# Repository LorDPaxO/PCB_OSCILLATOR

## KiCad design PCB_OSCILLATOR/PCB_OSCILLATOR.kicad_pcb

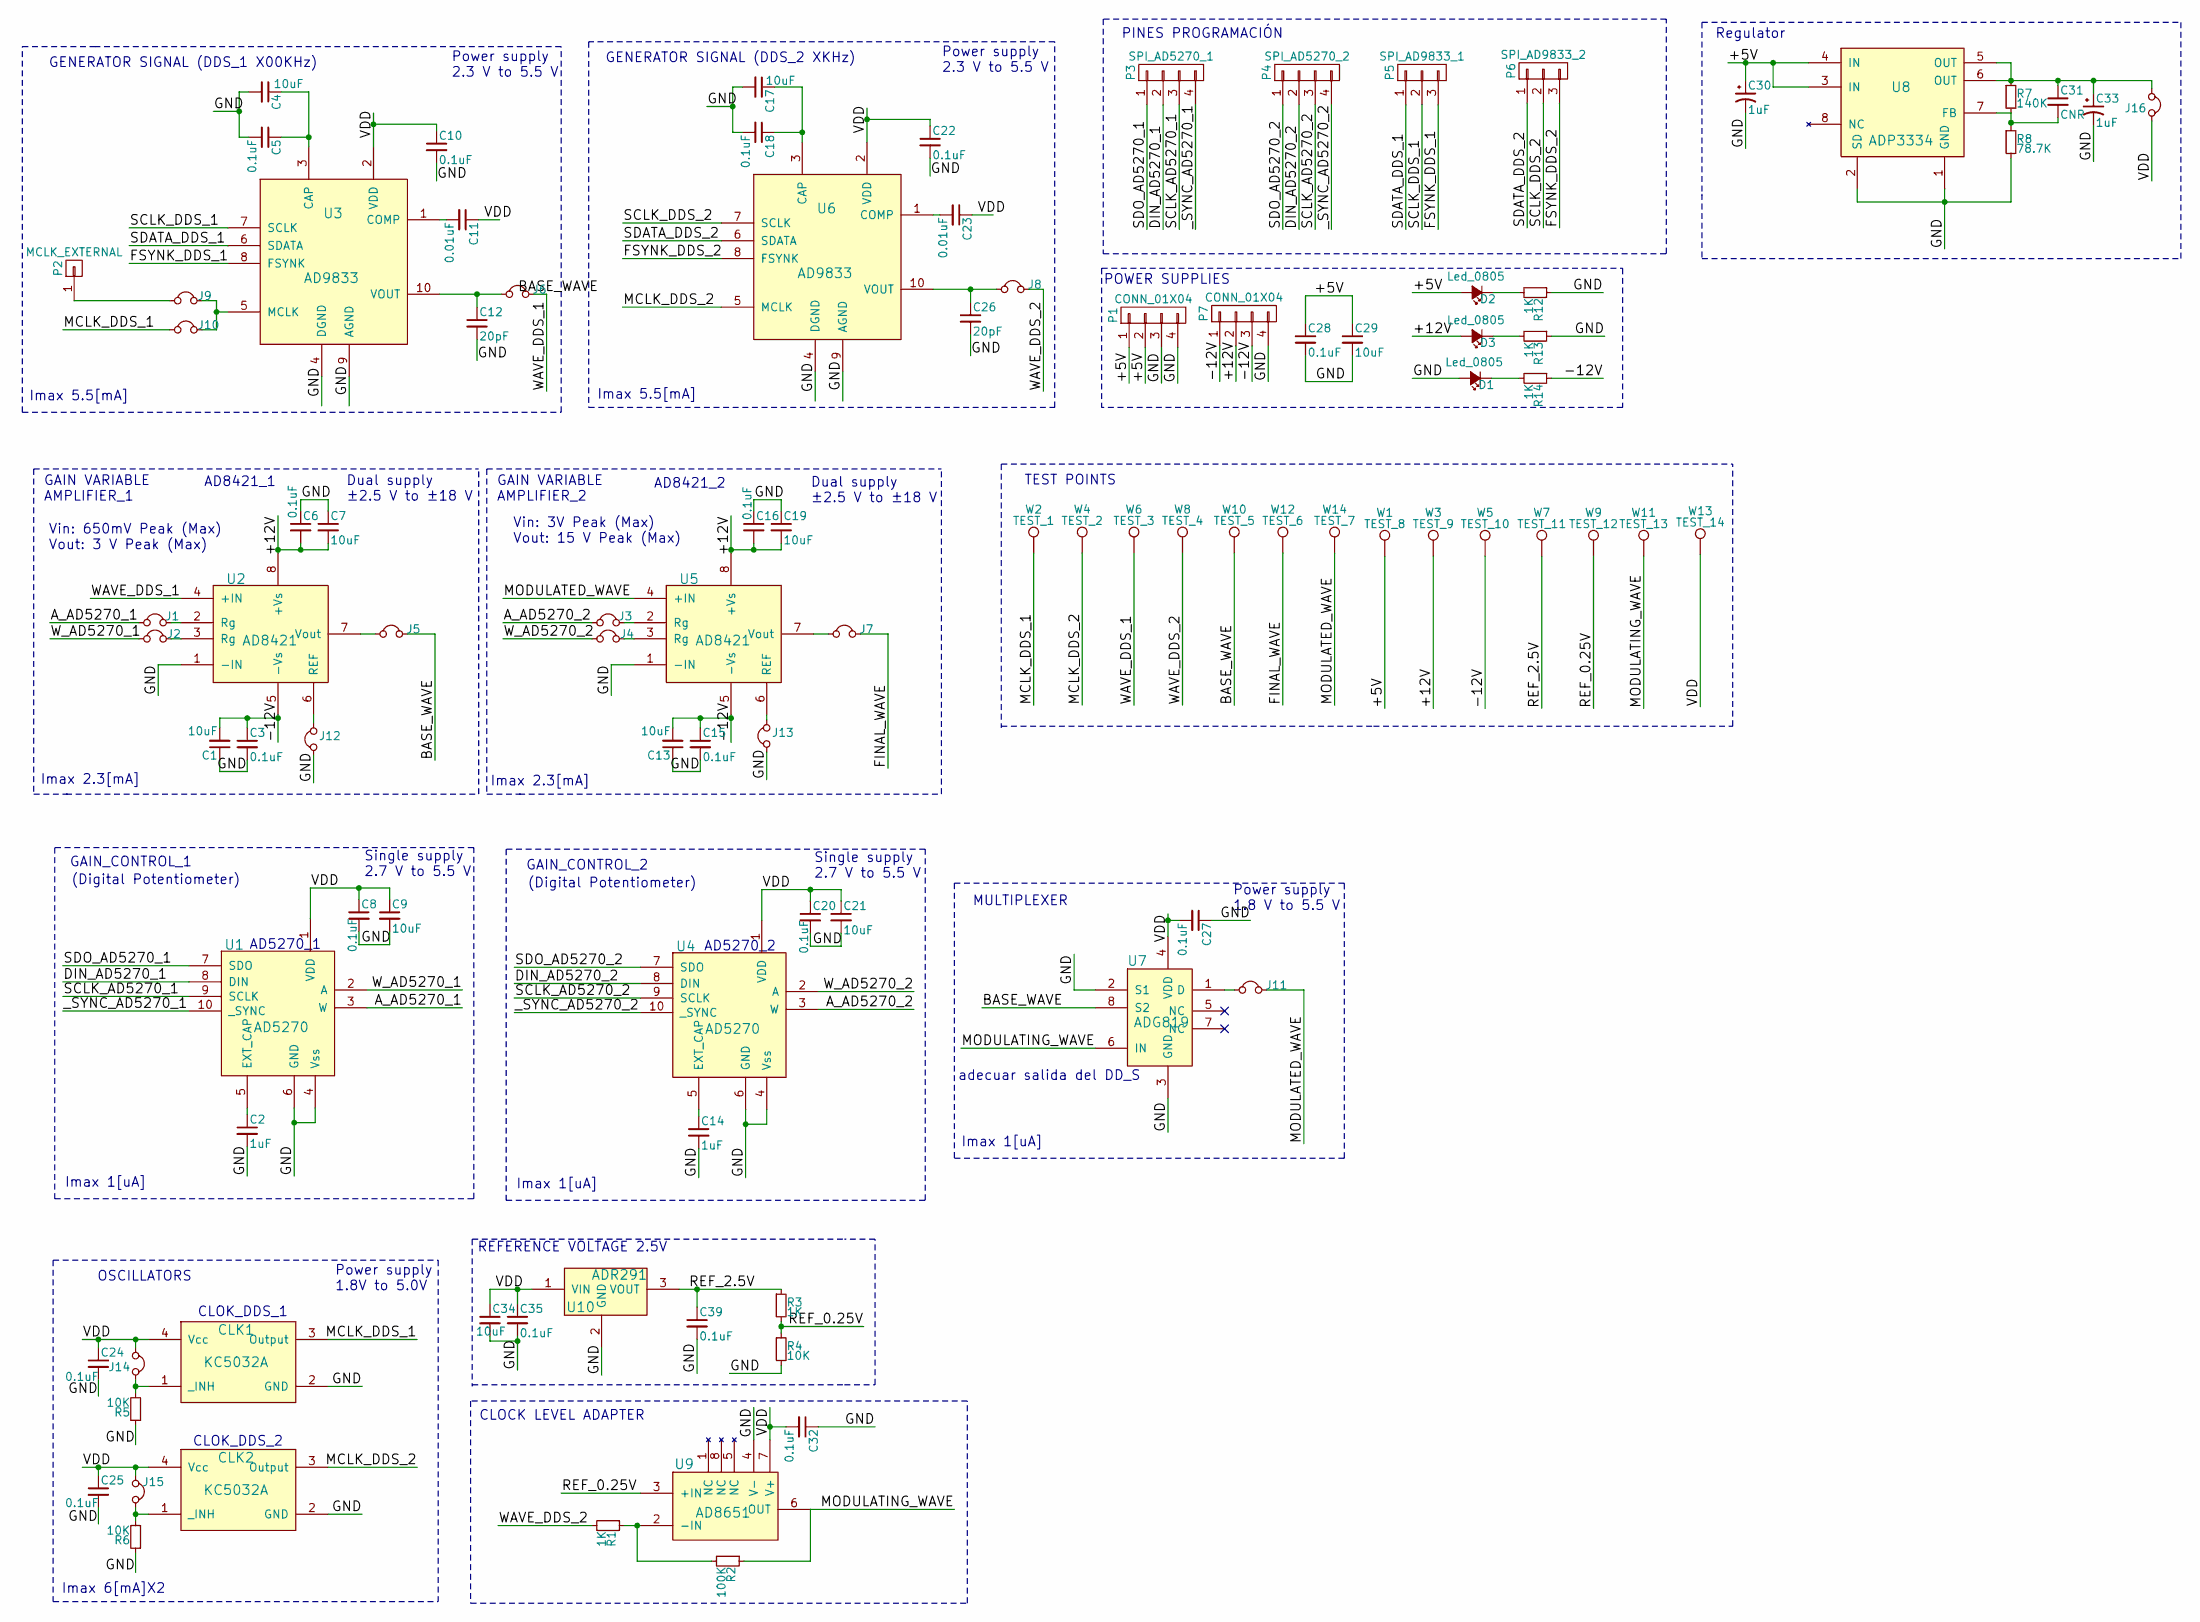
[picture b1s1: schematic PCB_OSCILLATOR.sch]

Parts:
C1, C7, C13, C19, C21: 10uF; C_1206_HandSoldering
C2, C14, C30, C33: 1uF; C_0805_HandSoldering
C3, C5, C6, C8, C10, C15, C16, C18, C20, C22, C24, C25, C27, C28, C32, C35, C39: 0.1uF; C_0805_HandSoldering; Digi-Key Part Number 478-1395-2-ND
C4, C9, C17, C29, C34: 10uF; C_0805_HandSoldering
C11, C23: 0.01uF; C_0805_HandSoldering; Digi-Key Part Number 478-1383-2-ND
C12, C26: 20pF; C_0805_HandSoldering
C31: CNR; C_1206_HandSoldering
CLK1, CLK2: KC5032A; KC5032A_Foot_Print
D1, D2, D3: Led_0805; R_0805_HandSoldering; Digi-Key Part Number 475-1410-2-ND
J1, J2, J3, J4, J5, J6, J7, J8, J9, J10, J11, J12, J13, J14, J15, J16: Jumper; Pin_Header_Straight_1x02
P1, P7: CONN_01X04; Socket_Strip_Straight_1x04
P2: MCLK_EXTERNAL; Socket_Strip_Straight_1x01
P3: SPI_AD5270_1; Socket_Strip_Straight_1x04
P4: SPI_AD5270_2; Socket_Strip_Straight_1x04
P5: SPI_AD9833_1; Socket_Strip_Straight_1x03
P6: SPI_AD9833_2; Socket_Strip_Straight_1x03
R1, R3, R12, R13, R14: 1K; R_0805_HandSoldering
R2: 100K; R_0805_HandSoldering
R4, R5, R6: 10K; R_0805_HandSoldering
R7: 140K
R8: 78.7K
U1, U4: AD5270; MSOP-10_3x3mm_Pitch0.5mm
U2, U5: AD8421; SOIC-8_3.9x4.9mm_Pitch1.27mm
U3, U6: AD9833; MSOP-10_3x3mm_Pitch0.5mm
U7: ADG819; MSOP-8_3x3mm_Pitch0.65mm
U8: ADP3334; SOIC-8_3.9x4.9mm_Pitch1.27mm
U9: AD8651; SOIC-8_3.9x4.9mm_Pitch1.27mm
U10: ADR291; TO-92_Inline_Narrow_Oval
W1: TEST_8; Measurement_Point_Round-TH_Small
W2: TEST_1; Measurement_Point_Round-TH_Small
W3: TEST_9; Measurement_Point_Round-TH_Small
W4: TEST_2; Measurement_Point_Round-TH_Small
W5: TEST_10; Measurement_Point_Round-TH_Small
W6: TEST_3; Measurement_Point_Round-TH_Small
W7: TEST_11; Measurement_Point_Round-TH_Small
W8: TEST_4; Measurement_Point_Round-TH_Small
W9: TEST_12; Measurement_Point_Round-TH_Small
W10: TEST_5; Measurement_Point_Round-TH_Small
W11: TEST_13; Measurement_Point_Round-TH_Small
W12: TEST_6; Measurement_Point_Round-TH_Small
W13: TEST_14; Measurement_Point_Round-TH_Small
W14: TEST_7; Measurement_Point_Round-TH_Small

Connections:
/+5V: C28.1, C29.1, C30.1, D2.2 (A), P1.1, P1.2, U8.3 (IN), U8.4 (IN), W1.1
/+12V: C6.2, C7.2, C16.2, C19.2, D3.2 (A), P7.2, U2.8 (+Vs), U5.8 (+Vs), W3.1
/-12V: C1.2, C3.1, C13.2, C15.1, P7.1, P7.3, R14.1, U2.5 (-Vs), U5.5 (-Vs), W5.1
/A_AD5270_1: J1.2, U1.3 (W)
/A_AD5270_2: J3.2, U4.3 (W)
/BASE_WAVE: J5.1, U7.8 (S2), W10.1
/DIN_AD5270_1: P3.2, U1.8 (DIN)
/DIN_AD5270_2: P4.2, U4.8 (DIN)
/FINAL_WAVE: J7.1, W12.1
/FSYNK_DDS_1: P5.3, U3.8 (FSYNK)
/FSYNK_DDS_2: P6.3, U6.8 (FSYNK)
/GND: C1.1, C2.2, C3.2, C4.2, C5.2, C6.1, C7.1, C8.2, C9.2, C10.2, C12.2, C13.1, C14.2, C15.2, C16.1, C17.2, C18.2, C19.1, C20.2, C21.2, C22.2, C24.2, C25.2, C26.2, C27.1, C28.2, C29.2, C30.2, C32.1, C33.2, C34.2, C35.2, C39.2, CLK1.2 (GND), CLK2.2 (GND), D1.2 (A), J12.2, J13.2, P1.3, P1.4, P7.4, R4.2, R5.1, R6.1, R8.2, R12.1, R13.1, U1.4 (Vss), U1.6 (GND), U2.1 (-IN), U3.4 (DGND), U3.9 (AGND), U4.4 (Vss), U4.6 (GND), U5.1 (-IN), U6.4 (DGND), U6.9 (AGND), U7.2 (S1), U7.3 (GND), U8.1 (GND), U8.2 (SD), U9.4 (V-), U10.2 (GND)
/MCLK_DDS_1: CLK1.3 (Output), J10.2, W2.1
/MCLK_DDS_2: CLK2.3 (Output), U6.5 (MCLK), W4.1
/MODULATED_WAVE: J11.1, U5.4 (+IN), W14.1
/MODULATING_WAVE: R2.1, U7.6 (IN), U9.6 (OUT), W11.1
/REF_0.25V: R3.2, R4.1, U9.3 (+IN), W9.1
/REF_2.5V: C39.1, R3.1, U10.3 (VOUT), W7.1
/SCLK_AD5270_1: P3.3, U1.9 (SCLK)
/SCLK_AD5270_2: P4.3, U4.9 (SCLK)
/SCLK_DDS_1: P5.2, U3.7 (SCLK)
/SCLK_DDS_2: P6.2, U6.7 (SCLK)
/SDATA_DDS_1: P5.1, U3.6 (SDATA)
/SDATA_DDS_2: P6.1, U6.6 (SDATA)
/SDO_AD5270_1: P3.1, U1.7 (SDO)
/SDO_AD5270_2: P4.1, U4.7 (SDO)
/VDD: C8.1, C9.1, C10.1, C11.1, C20.1, C21.1, C22.1, C23.1, C24.1, C25.1, C27.2, C32.2, C34.1, C35.1, CLK1.4 (Vcc), CLK2.4 (Vcc), J14.2, J15.2, J16.1, U1.1 (VDD), U3.2 (VDD), U4.1 (VDD), U6.2 (VDD), U7.4 (VDD), U9.7 (V+), U10.1 (VIN), W13.1
/WAVE_DDS_1: J6.1, U2.4 (+IN), W6.1
/WAVE_DDS_2: J8.1, R1.2, W8.1
/W_AD5270_1: J2.2, U1.2 (A)
/W_AD5270_2: J4.2, U4.2 (A)
/_SYNC_AD5270_1: P3.4, U1.10 (_SYNC)
/_SYNC_AD5270_2: P4.4, U4.10 (_SYNC)
unnamed: C2.1, U1.5 (EXT_CAP)
unnamed: C4.1, C5.1, U3.3 (CAP)
unnamed: C11.2, U3.1 (COMP)
unnamed: C12.1, J6.2, U3.10 (VOUT)
unnamed: C14.1, U4.5 (EXT_CAP)
unnamed: C17.1, C18.1, U6.3 (CAP)
unnamed: C23.2, U6.1 (COMP)
unnamed: C26.1, J8.2, U6.10 (VOUT)
unnamed: C31.1, C33.1, J16.2, R7.1, U8.5 (OUT), U8.6 (OUT)
unnamed: C31.2, R7.2, R8.1, U8.7 (FB)
unnamed: CLK1.1 (_INH), J14.1, R5.2
unnamed: CLK2.1 (_INH), J15.1, R6.2
unnamed: D1.1 (K), R14.2
unnamed: D2.1 (K), R12.2
unnamed: D3.1 (K), R13.2
unnamed: J1.1, U2.2 (Rg)
unnamed: J2.1, U2.3 (Rg)
unnamed: J3.1, U5.2 (Rg)
unnamed: J4.1, U5.3 (Rg)
unnamed: J5.2, U2.7 (Vout)
unnamed: J7.2, U5.7 (Vout)
unnamed: J9.2, P2.1
unnamed: J9.1, J10.1, U3.5 (MCLK)
unnamed: J11.2, U7.1 (D)
unnamed: J12.1, U2.6 (REF)
unnamed: J13.1, U5.6 (REF)
unnamed: R1.1, R2.2, U9.2 (-IN)

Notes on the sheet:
GENERATOR SIGNAL (DDS_1 X00KHz)
GENERATOR SIGNAL (DDS_2 XKHz)
OSCILLATORS
CLOK_DDS_1
CLOK_DDS_2
GAIN VARIABLE AMPLIFIER_1
Vin: 650mV Peak (Max) Vout: 3 V Peak (Max)
Vin: 3V Peak (Max) Vout: 15 V Peak (Max)
AD8421_1
AD8421_2
MULTIPLEXER
GAIN_CONTROL_1
(Digital Potentiometer)
AD5270_1
AD5270_2
PINES PROGRAMACIÓN
TEST POINTS
POWER SUPPLIES
GAIN_CONTROL_2
GAIN VARIABLE AMPLIFIER_2
Power supply 2.3 V to 5.5 V
adecuar salida del DD_S
Dual supply ±2.5 V to ±18 V
Power supply 1.8V to 5.0V
Single supply 2.7 V to 5.5 V
Power supply 1.8 V to 5.5 V
Imax 5.5[mA]
Imax 2.3[mA]
Imax 6[mA]X2
Imax 1[uA]
REFERENCE VOLTAGE 2.5V
CLOCK LEVEL ADAPTER
Regulator

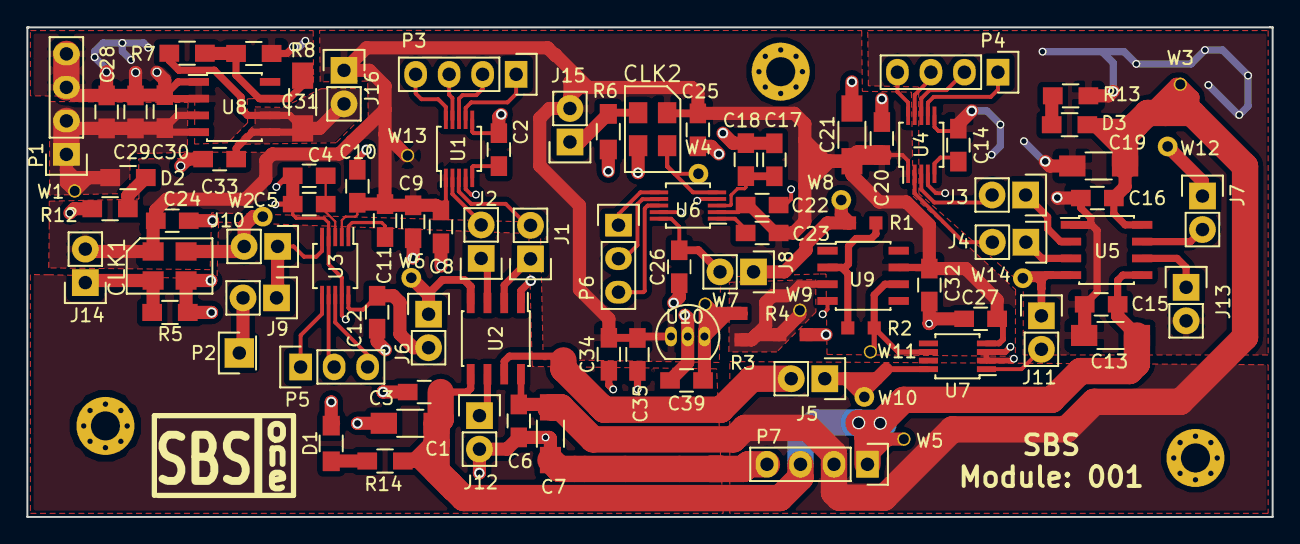
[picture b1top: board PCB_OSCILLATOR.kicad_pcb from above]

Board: 2 copper layers, 94.4 x 37.1 mm, 99 parts (0 on the bottom side), 60 nets.

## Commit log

2017-05-05 AD9833
    Avance de oscilador principal y auxliar.
2017-05-05 MCLK+
    Se agregan los osciladores para los MCLK de los DDS
2017-05-05 AD8421_UPDATE
    Se incluye la etapa de preamplificación y amplificación
2017-05-05 Incluyo el ADG849
    Nombro algunas señales adicionales
2017-05-05 Esquematico casi final
    faltan agregar los leds que indiquen presencia de alimentación
2017-05-05 Esquematico completo
    Primera versión de todo el esquematico, falta revisión del grupo
2017-05-08 Descripción y pruebas BOM
2017-05-08 Another version
2017-05-08 Faltan Cambios Menores
    Voy a hacer simulaciones con el ADG819 y diagrama de bloques para
    corregir errores y verificar si hacen falta poner algunos test points.
2017-05-09 Adjunto Diagrama de bloques
    Está en carpeta principal con el nombre de las señales.
    Falta Validar funcionamiento del ADG819 y agregar puntos para pruebas
    (pines, sin contar los test points)
2017-05-09 Primera Versión completa con diagrama de bloques en carpeta principal
    //
2017-05-09 SEGREGANDO ELEMENTOS SIN VER CAMINOS NI CAPACITORES
2017-05-11 Faltan Hacer correciones que están en trello
    Terminar correciones y pasar a la etapa de segregación de elementos,
    layout final propuesto para el viernes 12
2017-05-12 Algunos cambios Adicionales
    //
2017-05-13 Pequeñas correciones
    Cambio de Huellas de capacitores
    Correción de footPrint de jumpers con errores
2017-05-13 Inicio de borrador de ruteado
    //
2017-05-13 Avance pequeño
    //
2017-05-14 Board al 70%
    // =)
2017-05-14 Avance
    Falta poner regulador y ultimas etapas.
    80% Definir bien puntos para regulador y alimentación.
2017-05-15 Pequeños cambios//
    //Queda pendiente para mañana
2017-05-15 80% PCB
    Terminar conexiones de alimentación, regletas de +12 -12
    y tratar de hacer el plano completo para tierra
2017-05-15 PCB 90%
    Reacomodar elementos y hacer planos para power integrity y plano de GND
    completo por la parte de abajo
2017-05-16 PCB 95%
    Terminar de hacer planos que se crean convenientes//
2017-05-16 98% Completed
2017-05-16 PBC 99%
    Faltan solo vias para conectar planos de tierras (Definir si se hace
    plano de tierrta a la parte inferior izquierda//
2017-05-16 //
    //
2017-05-17 PCB 100%
    Planos terminados, vias faltantes agregadas, colocación de los nombres,
    falta realizar una última revisión para tratar de identificar errores y
    depurarlos.
2017-05-17 PCB VERSION 1
    Versión para imprimir de pcb
2017-05-18 Cambio de regulador en esquematico
    //
2017-05-18 Ultima Version
    //
